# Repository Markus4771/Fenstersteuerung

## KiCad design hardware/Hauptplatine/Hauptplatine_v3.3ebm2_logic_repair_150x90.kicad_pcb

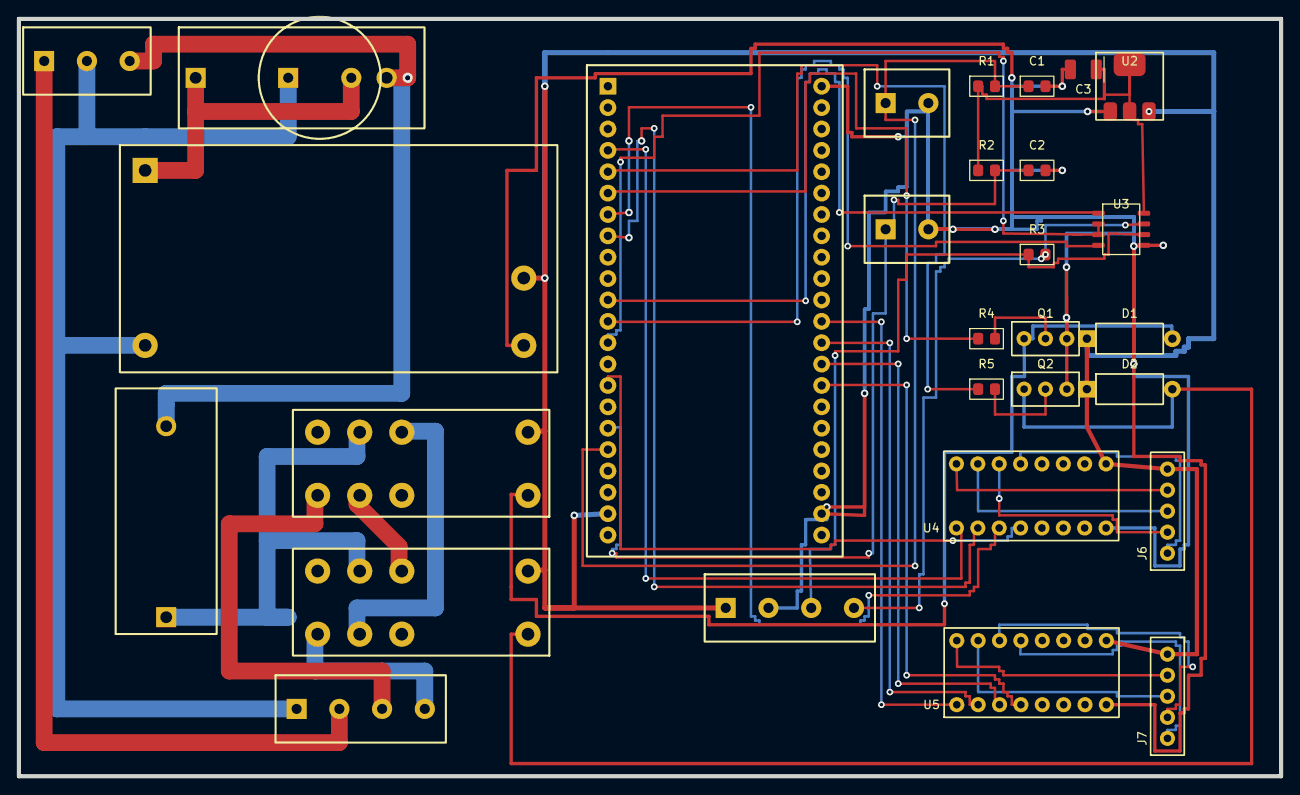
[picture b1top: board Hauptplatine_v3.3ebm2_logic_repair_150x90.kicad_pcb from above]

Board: 2 copper layers, 150.0 x 90.0 mm, 30 parts (0 on the bottom side), 41 nets.

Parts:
C1, C2: 100n; C_0805_2012Metric
C3: 22uF 10V TANT; CP_EIA-3528-21_Kemet-B
D1, D2: 1N4007; D_DO-41_SOD81_P10.16mm_Horizontal
F1: T1A; Littelfuse_646_5x20
F2: T2A; Littelfuse_646_5x20
J1: 230V IN L/N/PE; Phoenix_MKDS-1.5_3P_P5.08
J2: REED OFFEN; Phoenix_MKDS-1.5_2P_P5.08
J3: REED GEKIPPT; Phoenix_MKDS-1.5_2P_P5.08
J4: RS485 5V/GND/A/B; Phoenix_MKDS-1.5_4P_P5.08
J5: MOTOR N/PE/AUF/AB; Phoenix_MKDS-1.5_4P_P5.08
J6: 28BYJ-48 OBEN; JST_XH_B5B-XH-A_1x05_P2.50mm_Vertical
J7: 28BYJ-48 UNTEN; JST_XH_B5B-XH-A_1x05_P2.50mm_Vertical
K1: Finder 40.52.9.005.0000 AUF; Relay_DPDT_Finder_40.52
K2: Finder 40.52.9.005.0000 AB; Relay_DPDT_Finder_40.52
PS1: IRM-20-5; Converter_ACDC_MeanWell_IRM-20-xx_THT
Q1: BC337 AUF; TO-92_Inline_Wide
Q2: BC337 AB; TO-92_Inline_Wide
R1, R2: 10k; R_0805_2012Metric
R3: 120R TERM; R_0805_2012Metric
R4, R5: 470R; R_0805_2012Metric
RV1: MOV 275VAC; MOV_S14K275_P7.5
U1: ESP32-S3 DevKitC-1 headers; ESP32-S3_DevKitC-1_Carrier
U2: AMS1117-3.3; SOT-223-3_TabPin2
U3: MAX3485; SOIC-8_3.9x4.9mm_P1.27mm
U4: ULN2003A OBEN; DIP-16_W7.62mm
U5: ULN2003A UNTEN; DIP-16_W7.62mm

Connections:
/+3V3: C3.1, R1.1, R2.1, U2.2, U3.8
/+5V: D1.1, D2.1, J4.1, J6.5, J7.5, K1.A2, K2.A2, PS1.4 (+Vo), U1.41, U2.3, U4.9, U5.9
/AC_L: F1.2, F2.2, J1.3
/AC_N: J1.2, J5.1, PS1.2 (AC/N), RV1.1
/BOT_COIL_1: J7.4, U5.16
/BOT_COIL_2: J7.3, U5.15
/BOT_COIL_3: J7.2, U5.14
/BOT_COIL_4: J7.1, U5.13
/DN_FEED: K1.22, K2.11
/GND: C1.2, C2.2, C3.2, J2.2, J3.2, J4.2, PS1.3 (-Vo), Q1.3, Q2.3, U1.2, U1.42, U2.1, U3.5, U4.8, U5.8
/K1_COIL_LOW: D1.2, K1.A1, Q1.1
/K2_COIL_LOW: D2.2, K2.A1, Q2.1
/L_MOTOR: F2.1, K1.21, K2.21
/L_PSU_FUSED: F1.1, PS1.1 (AC/L), RV1.2
/MOTOR_DN: J5.4, K2.14
/MOTOR_UP: J5.3, K1.14
/PE: J1.1, J5.2
/Q1_BASE: Q1.2, R4.2
/Q2_BASE: Q2.2, R5.2
/REED_OPEN: C1.1, J2.1, R1.2, U1.35
/REED_TILT: C2.1, J3.1, R2.2, U1.33
/ROLL_DN: R5.1, U1.9
/ROLL_UP: R4.1, U1.11
/RS485_A: J4.3, R3.1, U3.6
/RS485_B: J4.4, R3.2, U3.7
/RS485_DE: U1.25, U3.2, U3.3
/RS485_RX: U1.21, U3.1
/RS485_TX: U1.23, U3.4
/STEP_BOT_1: U1.24, U5.1
/STEP_BOT_2: U1.26, U5.2
/STEP_BOT_3: U1.28, U5.3
/STEP_BOT_4: U1.30, U5.4
/STEP_TOP_1: U1.7, U4.1
/STEP_TOP_2: U1.15, U4.2
/STEP_TOP_3: U1.13, U4.3
/STEP_TOP_4: U1.29, U4.4
/TOP_COIL_1: J6.4, U4.16
/TOP_COIL_2: J6.3, U4.15
/TOP_COIL_3: J6.2, U4.14
/TOP_COIL_4: J6.1, U4.13
/UP_FEED: K1.11, K2.22
